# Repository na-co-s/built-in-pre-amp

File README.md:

# na-co's built-in pre amp
Pre amp for embedding in guitar. Replace the output jack with TRS and supply +12V to the ring for use.

https://yokuhizumu.art.blog/

## Connectors
### J1, J2 and U2 (Top view)
- J1: Connect to pickup selector
- J2: Connect to LED (Resistor is required)
- U2: Connect to dual triode vacuum tube

|||
|---|---|
|(J1) GND|(J1) IN|
|(J2) GND|(J2) +12V|
|(U2) GND|(U2) +12V|
|(U2) GND|(U2) K1|
|(U2) G2|(U2) G1|
|(U2) P2|(U2) P1|

### RV1, RV2, RV3, J3 and J4 (Top view)
- J3: Connect to output TRS jack (Sleeve and Tip)
- J4: Connect to output TRS jack (Ring)

|||
|---|---|
|(RV2) VOLUME IN|(J4) +12V|
|(RV2) VOLUME OUT|(J3) OUT|
|(RV2) GND|(J3) GND|
|(RV1) GAIN IN|(RV3) TONE IN|
|(RV1) GAIN OUT|(RV3) TONE OUT|
|(RV1) GND|(RV3) N.C.|

### J5
- J5: Connect to external voltage source for plate (Option)

## Jumpers
### JP1 Relay
If a short pin is connected to pins 1-2, the relay will always be energized as long as +12V is supplied to J4.  
If a footswitch is connected to pins 1-2, the relay will be energized only when the footswitch is on.  

### JP2 Plate Voltage
If a short pin is connected to pins 1-2, +12V supplied to J4 will be supplied to the plate.  
If a short pin is connected to pins 2-3 and an external voltage is supplied to J5, that voltage will be supplied to the plate.  

## BOM
|Ref|Val|
|---|---|
|K1|EA2-12NU|
|U1|LM386N-4|
|U2|12AU7|
|R1|1K|
|R2|100K|
|R3|470K|
|R4|47K|
|C1|223|
|C2|223|
|C3|223|
|C4|223|
|RV1|A250K|
|RV2|A250K|
|RV3|A250K|

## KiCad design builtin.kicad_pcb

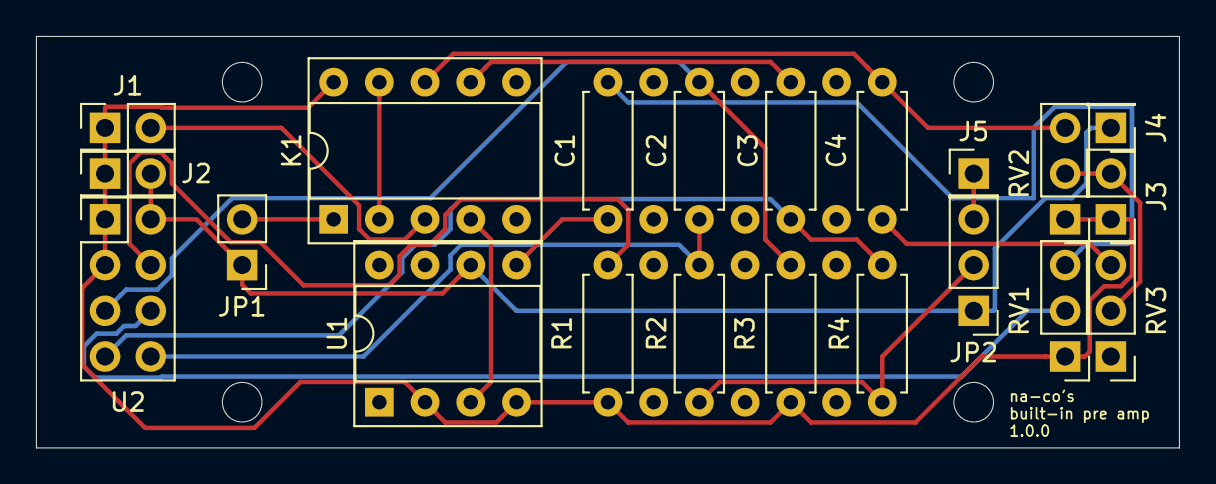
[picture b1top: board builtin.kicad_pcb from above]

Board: 2 copper layers, 63.5 x 22.9 mm, 21 parts (0 on the bottom side), 19 nets.

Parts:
C1, C2, C3, C4: 223; R_Axial_DIN0207_L6.3mm_D2.5mm_P7.62mm_Horizontal
J1: INPUT; PinHeader_2x01_P2.54mm_Vertical
J2: LED; PinHeader_2x01_P2.54mm_Vertical
J3: OUTPUT; PinHeader_1x02_P2.54mm_Vertical
J4: +12V; PinHeader_1x01_P2.54mm_Vertical
J5: PLATE VOLTAGE; PinHeader_1x01_P2.54mm_Vertical
JP1: Foot Switch; PinHeader_1x02_P2.54mm_Vertical
JP2: Plate Voltage; PinHeader_1x03_P2.54mm_Vertical
K1: Bypass; DIP-10_W7.62mm_Socket
R1: 1K; R_Axial_DIN0207_L6.3mm_D2.5mm_P7.62mm_Horizontal
R2: 100K; R_Axial_DIN0207_L6.3mm_D2.5mm_P7.62mm_Horizontal
R3: 470K; R_Axial_DIN0207_L6.3mm_D2.5mm_P7.62mm_Horizontal
R4: 47K; R_Axial_DIN0207_L6.3mm_D2.5mm_P7.62mm_Horizontal
RV1: GAIN; PinHeader_1x03_P2.54mm_Vertical
RV2: VOLUME; PinHeader_1x03_P2.54mm_Vertical
RV3: TONE; PinHeader_1x03_P2.54mm_Vertical
U1: LM386; DIP-8_W7.62mm_Socket
U2: ECC83; PinHeader_2x04_P2.54mm_Vertical

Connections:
+12V: J2.2, J4.1, JP1.1, JP2.1, U1.6, U2.5
GND: J1.1, J2.1, J3.1, K1.10, R1.2, R3.2, RV1.1, RV2.1, U1.2, U1.4, U2.3, U2.4
unnamed: C1.1, U1.5
unnamed: C1.2, RV1.3
unnamed: C2.1, R2.2, U2.6
unnamed: C2.2, R3.1, U2.2
unnamed: C3.1, R4.2, U2.1
unnamed: C3.2, K1.7
unnamed: C4.1, K1.8, RV2.3
unnamed: C4.2, RV3.3
unnamed: J1.2, K1.3
unnamed: J3.2, RV2.2, RV3.2
unnamed: J5.1, JP2.3
unnamed: JP1.2, K1.1
unnamed: JP2.2, R2.1, R4.1
unnamed: K1.2, K1.9
unnamed: K1.4, U1.3
unnamed: R1.1, U2.8
unnamed: RV1.2, U2.7

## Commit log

2020-02-04 2020-02-04 11:19:35
